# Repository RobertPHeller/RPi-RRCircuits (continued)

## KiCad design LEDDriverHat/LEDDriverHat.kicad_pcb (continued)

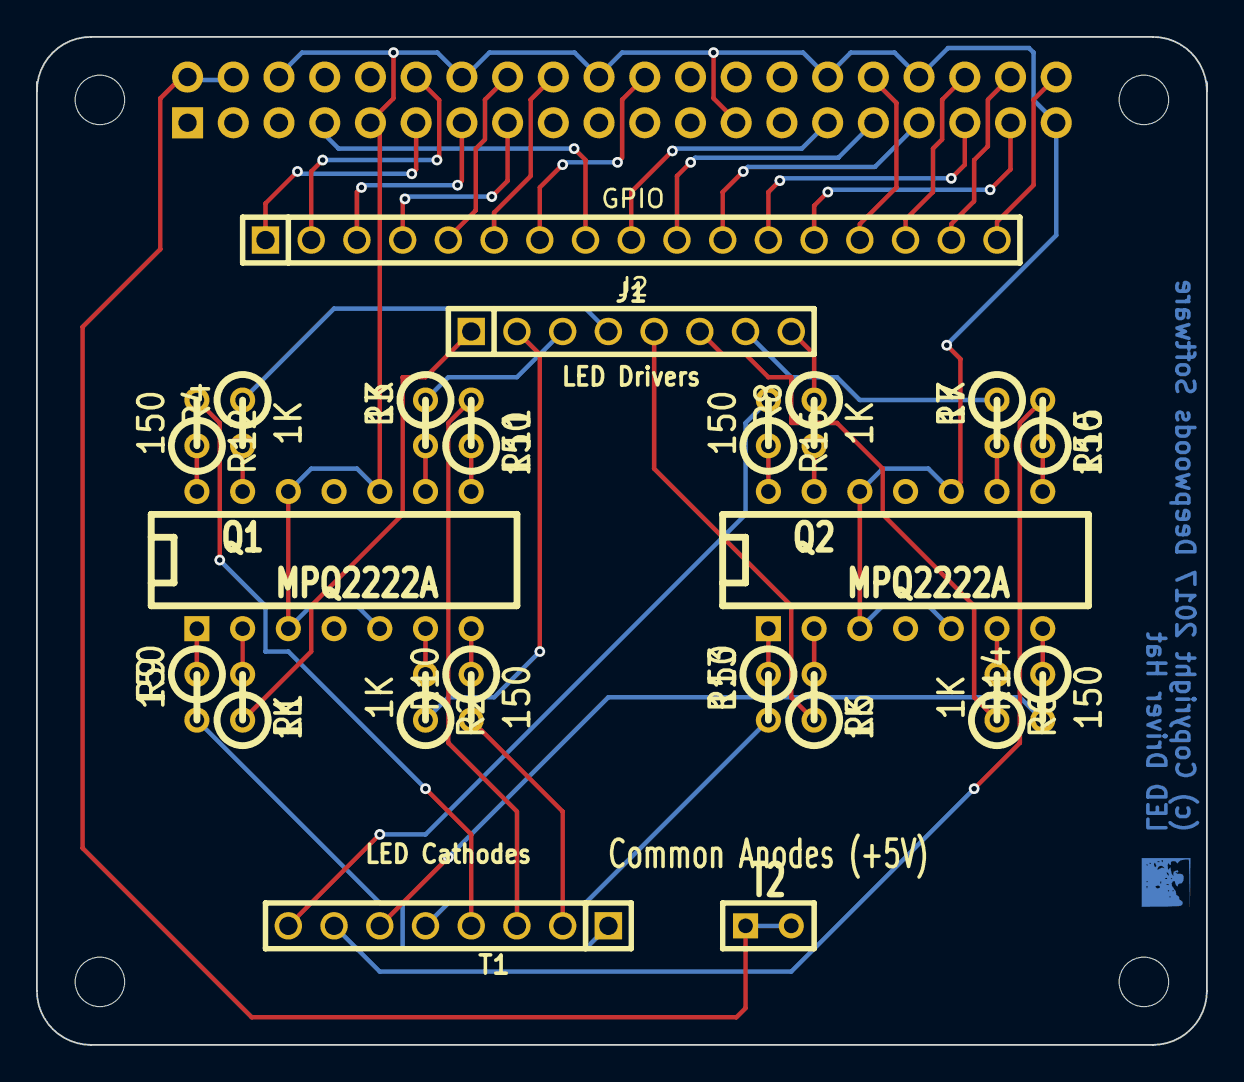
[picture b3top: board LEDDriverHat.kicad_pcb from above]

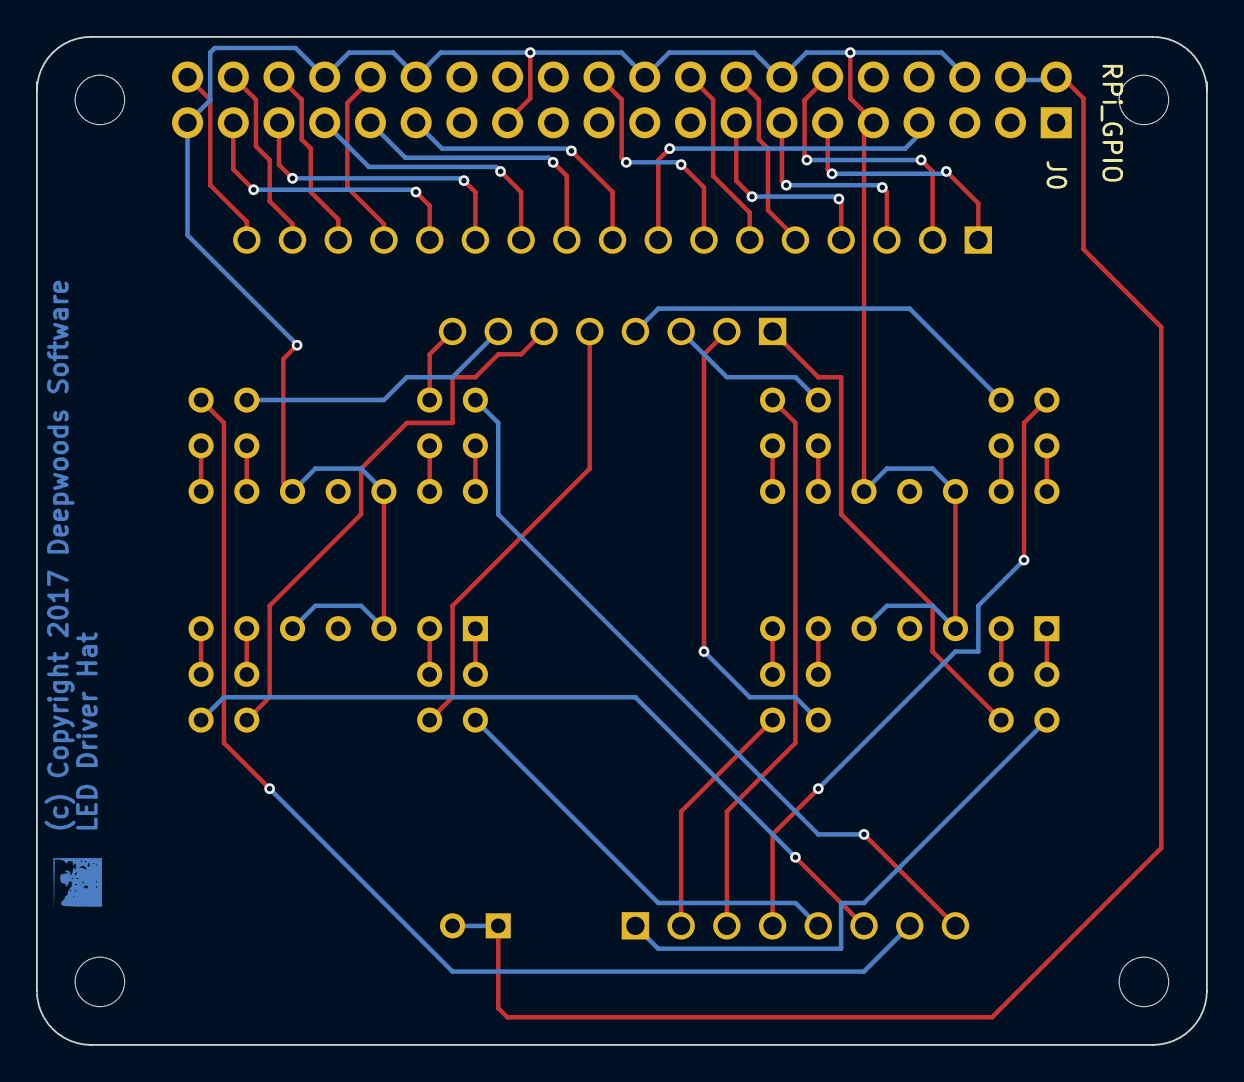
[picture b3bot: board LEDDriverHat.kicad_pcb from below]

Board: 2 copper layers, 65.0 x 56.0 mm, 27 parts (5 on the bottom side), 51 nets.

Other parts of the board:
H1, H2, H3, H4: RPi_Hat_Mounting_Hole

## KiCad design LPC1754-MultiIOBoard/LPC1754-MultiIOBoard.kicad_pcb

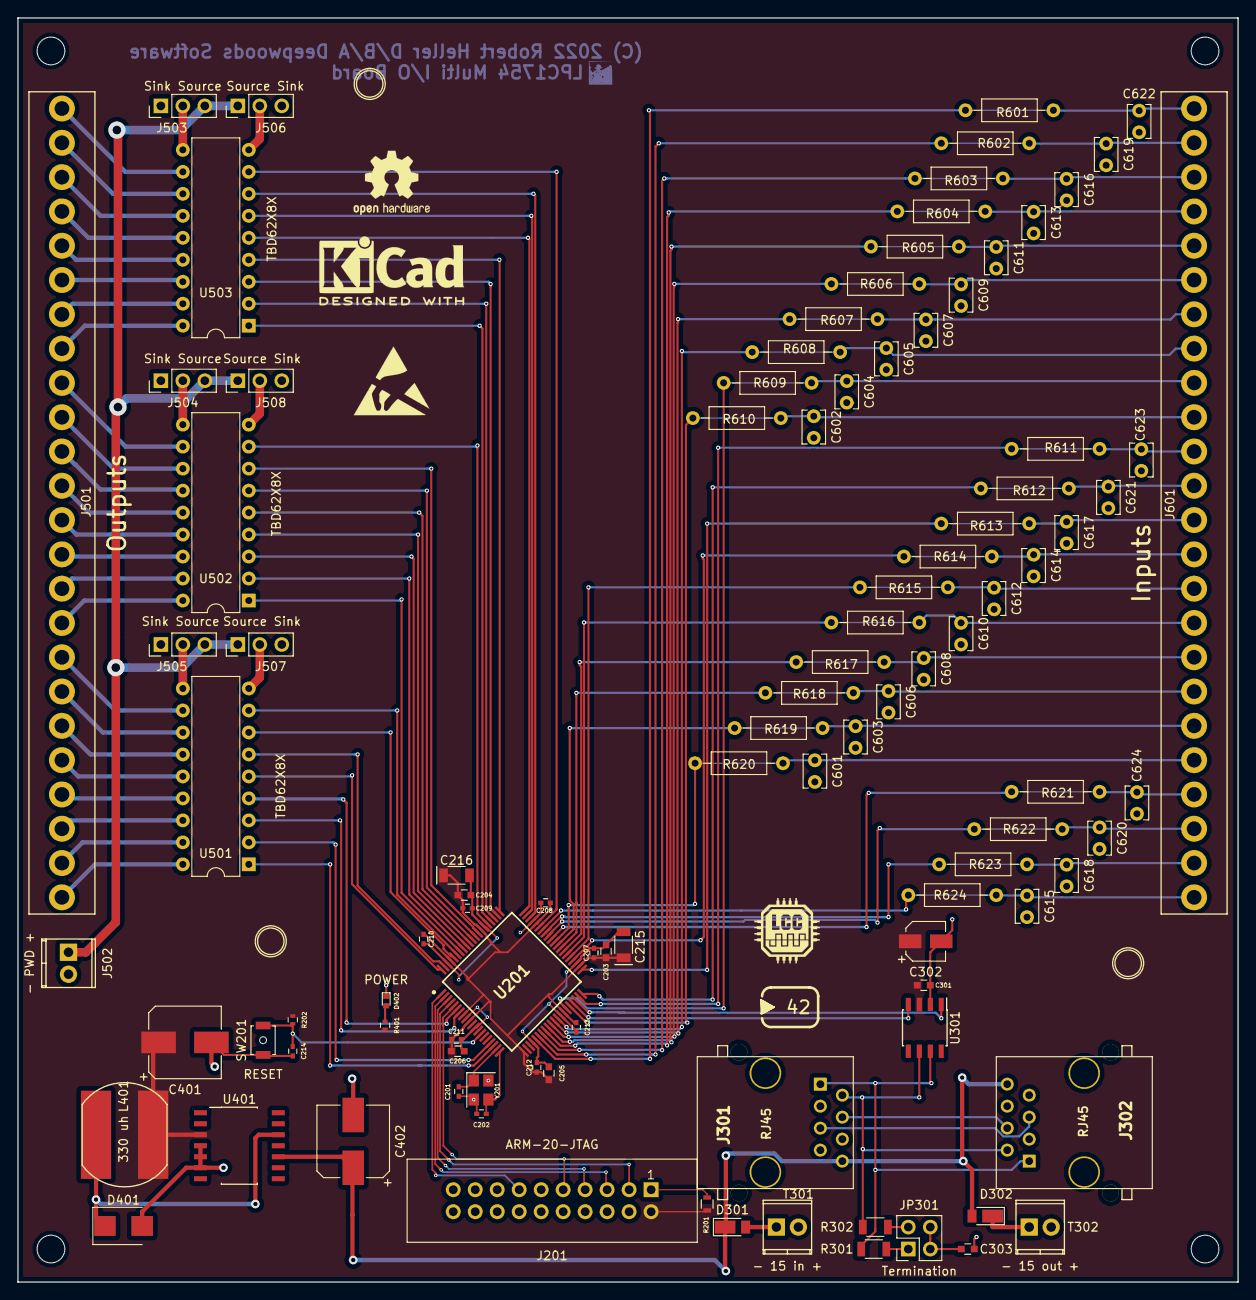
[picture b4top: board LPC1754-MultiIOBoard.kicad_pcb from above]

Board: 2 copper layers, 141.0 x 146.1 mm, 102 parts (0 on the bottom side), 128 nets.

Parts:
C201: 18 pF; C_0402
C202: 18pf; C_0402
C203, C204, C205, C206: 1uf; C_0603
C207, C208, C209, C210, C211, C212, C213: 100nf; C_0402
C214: 1uf; C_0402
C215, C216: 10 uf; C_POL_1206
C301: .1 uf; C_0603
C302: 15 uf 15V; CP_Elec_4x5.7
C303: 47 nf; C_0603
C401: 220 uf 25V; CP_Elec_8x10
C402: 22 uf 100V; CP_Elec_8x10
C601, C602, C603, C604, C605, C606, C607, C608, C609, C610, C611, C612, C613, C614, C615, C616, C617, C618, C619, C620, C621, C622, C623, C624: C; C_Disc_D3.8mm_W2.6mm_P2.50mm
D301, D302: DFLS240-7; D_PowerDI-123
D401: CMSH1-60 TR13; D_SMB
D402: POWER; LED_0402
J201: ARM-20-JTAG; IDC_Header_Straight_20pins
J301, J302: RJ45; RJ45_8N-S
J501: Outputs; Molex_KK_396_01x24_3.96mm_RightAngle
J502: - PWD +; TerminalBlock_Pheonix_MPT-2.54mm_2pol
J503, J504, J505: Sink Source; Pin_Header_Straight_1x03_Pitch2.54mm
J506, J507, J508: Source Sink; Pin_Header_Straight_1x03_Pitch2.54mm
J601: Inputs; Molex_KK_396_01x24_3.96mm_RightAngle
JP301: Termination; Pin_Header_Straight_2x02_Pitch2.54mm
L401: 330 uh; SRN1060
R201: 0; R_0603
R202: 10K; R_0402
R301, R302: 60 Ohms; R_1206
R401: 330; R_0402
R601, R602, R603, R604, R605, R606, R607, R608, R609, R610, R611, R612, R613, R614, R615, R616, R617, R618, R619, R620, R621, R622, R623, R624: 0; R_Axial_DIN0207_L6.3mm_D2.5mm_P10.16mm_Horizontal_WJumper
SW201: RESET; SW_SPST_B3U-1000P-B
T301: - 15 in +; TerminalBlock_Pheonix_MPT-2.54mm_2pol
T302: - 15 out +; TerminalBlock_Pheonix_MPT-2.54mm_2pol
U201: LPC1754FBD80,551; QFP50P1400X1400X160-80N
U301: TCAN332DR; SOIC-8_3.9x4.9mm_Pitch1.27mm
U401: LM2574N-3.3; SOIC-14_7.4x8.7mm_Pitch1.27mm
U501, U502, U503: TBD62X8X; DIP-18_W7.62mm
Y201: 25MHZ; Crystal_SMD_Abracon_ABM8G-4pin_3.2x2.5mm

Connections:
+3V3: C203.1, C204.1, C205.1, C206.1, C207.1, C208.1, C209.1, C210.1, C211.1, C212.1, C213.1, C215.1, C216.1, C301.1, C302.1, C401.1, J201.2, L401.2, R201.2, R202.1, R401.2, U201.8, U201.10, U201.21, U201.34, U201.42, U201.56, U201.67, U201.77, U301.3, U401.3
+VDC: J502.1, J503.3, J504.3, J505.3, J506.1, J507.1, J508.1
/CAN Transceiver/CANH: J301.1, J302.1, R301.1, U301.7
/CAN Transceiver/CANL: J301.2, J302.2, R302.1, U301.6
/CAN Transceiver/CAN_RX: U201.37, U301.4
/CAN Transceiver/CAN_TX: U201.38, U301.1
/Micro Processor Unit/C0P0B0: R601.2, U201.25
/Micro Processor Unit/C0P0B1: R602.2, U201.26
/Micro Processor Unit/C0P0B2: R603.2, U201.27
/Micro Processor Unit/C0P0B3: R604.2, U201.28
/Micro Processor Unit/C0P0B4: R605.2, U201.29
/Micro Processor Unit/C0P0B5: R606.2, U201.30
/Micro Processor Unit/C0P0B6: R607.2, U201.31
/Micro Processor Unit/C0P0B7: R608.2, U201.32
/Micro Processor Unit/C0P1B0: R609.2, U201.35
/Micro Processor Unit/C0P1B1: R610.2, U201.36
/Micro Processor Unit/C0P1B2: R611.2, U201.39
/Micro Processor Unit/C0P1B3: R612.2, U201.40
/Micro Processor Unit/C0P1B4: R613.2, U201.41
/Micro Processor Unit/C0P1B5: R614.2, U201.44
/Micro Processor Unit/C0P1B6: R615.2, U201.45
/Micro Processor Unit/C0P1B7: R616.2, U201.46
/Micro Processor Unit/C0P2B0: R617.2, U201.47
/Micro Processor Unit/C0P2B1: R618.2, U201.48
/Micro Processor Unit/C0P2B2: R619.2, U201.49
/Micro Processor Unit/C0P2B3: R620.2, U201.50
/Micro Processor Unit/C0P2B4: R621.2, U201.51
/Micro Processor Unit/C0P2B5: R622.2, U201.52
/Micro Processor Unit/C0P2B6: R623.2, U201.53
/Micro Processor Unit/C0P2B7: R624.2, U201.54
/Micro Processor Unit/C1P0B0: U201.18, U501.1
/Micro Processor Unit/C1P0B1: U201.17, U501.2
/Micro Processor Unit/C1P0B2: U201.7, U501.3
/Micro Processor Unit/C1P0B3: U201.6, U501.4
/Micro Processor Unit/C1P0B4: U201.80, U501.5
/Micro Processor Unit/C1P0B5: U201.79, U501.6
/Micro Processor Unit/C1P0B6: U201.76, U501.7
/Micro Processor Unit/C1P0B7: U201.75, U501.8
/Micro Processor Unit/C1P1B0: U201.74, U502.1
/Micro Processor Unit/C1P1B1: U201.73, U502.2
/Micro Processor Unit/C1P1B2: U201.72, U502.3
/Micro Processor Unit/C1P1B3: U201.71, U502.4
/Micro Processor Unit/C1P1B4: U201.70, U502.5
/Micro Processor Unit/C1P1B5: U201.69, U502.6
/Micro Processor Unit/C1P1B6: U201.68, U502.7
/Micro Processor Unit/C1P1B7: U201.65, U502.8
/Micro Processor Unit/C1P2B0: U201.64, U503.1
/Micro Processor Unit/C1P2B1: U201.63, U503.2
/Micro Processor Unit/C1P2B2: U201.62, U503.3
/Micro Processor Unit/C1P2B3: U201.61, U503.4
/Micro Processor Unit/C1P2B4: U201.60, U503.5
/Micro Processor Unit/C1P2B5: U201.59, U503.6
/Micro Processor Unit/C1P2B6: U201.58, U503.7
/Micro Processor Unit/C1P2B7: U201.55, U503.8
CAN +12V: C402.1, D301.1, D302.2, J301.8, J302.8, U401.10
GND: C201.2, C202.2, C203.2, C204.2, C205.2, C206.2, C207.2, C208.2, C209.2, C210.2, C211.2, C212.2, C213.2, C214.2, C215.2, C216.2, C301.2, C302.2, C303.2, C401.2, C402.2, C601.2, C602.2, C603.2, C604.2, C605.2, C606.2, C607.2, C608.2, C609.2, C610.2, C611.2, C612.2, C613.2, C614.2, C615.2, C616.2, C617.2, C618.2, C619.2, C620.2, C621.2, C622.2, C623.2, C624.2, D401.2, D402.1, J201.4, J201.6, J201.8, J201.10, J201.12, J201.14, J201.16, J201.18, J201.20, J301.3, J301.6, J301.7, J302.3, J302.6, J302.7, J502.2, J503.1, J504.1, J505.1, J506.3, J507.3, J508.3, SW201.1, T301.2, T302.2, U201.9, U201.12, U201.24, U201.33, U201.43, U201.57, U201.66, U201.78, U301.2, U401.4, U401.5, U401.6, Y201.2, Y201.4
unnamed: C201.1, U201.19, Y201.1
unnamed: C202.1, U201.20, Y201.3
unnamed: C214.1, R202.2, SW201.2, U201.14
unnamed: C303.1, JP301.3, JP301.4
unnamed: C601.1, J601.20, R620.1
unnamed: C602.1, J601.10, R610.1
unnamed: C603.1, J601.19, R619.1
unnamed: C604.1, J601.9, R609.1
unnamed: C605.1, J601.8, R608.1
unnamed: C606.1, J601.18, R618.1
unnamed: C607.1, J601.7, R607.1
unnamed: C608.1, J601.17, R617.1
unnamed: C609.1, J601.6, R606.1
unnamed: C610.1, J601.16, R616.1
unnamed: C611.1, J601.5, R605.1
unnamed: C612.1, J601.15, R615.1
unnamed: C613.1, J601.4, R604.1
unnamed: C614.1, J601.14, R614.1
unnamed: C615.1, J601.24, R624.1
unnamed: C616.1, J601.3, R603.1
unnamed: C617.1, J601.13, R613.1
unnamed: C618.1, J601.23, R623.1
unnamed: C619.1, J601.2, R602.1
unnamed: C620.1, J601.22, R622.1
unnamed: C621.1, J601.12, R612.1
unnamed: C622.1, J601.1, R601.1
unnamed: C623.1, J601.11, R611.1
unnamed: C624.1, J601.21, R621.1
unnamed: D301.2, T301.1
unnamed: D302.1, T302.1
unnamed: D401.1, L401.1, U401.12
unnamed: D402.2, R401.1
unnamed: J201.1, R201.1
unnamed: J201.3, U201.4
unnamed: J201.5, U201.2
unnamed: J201.7, U201.3
unnamed: J201.9, U201.5
unnamed: J201.13, U201.1
unnamed: J301.4, J302.4
unnamed: J301.5, J302.5
unnamed: J501.1, U501.18
unnamed: J501.2, U501.17
unnamed: J501.3, U501.16
unnamed: J501.4, U501.15
unnamed: J501.5, U501.14
unnamed: J501.6, U501.13
unnamed: J501.7, U501.12
unnamed: J501.8, U501.11
unnamed: J501.9, U502.18
unnamed: J501.10, U502.17
unnamed: J501.11, U502.16
unnamed: J501.12, U502.15
unnamed: J501.13, U502.14
unnamed: J501.14, U502.13
unnamed: J501.15, U502.12
unnamed: J501.16, U502.11
unnamed: J501.17, U503.18
unnamed: J501.18, U503.17
unnamed: J501.19, U503.16
unnamed: J501.20, U503.15
unnamed: J501.21, U503.14
unnamed: J501.22, U503.13
unnamed: J501.23, U503.12
unnamed: J501.24, U503.11
unnamed: J503.2, U503.10
unnamed: J504.2, U502.10
unnamed: J505.2, U501.10
unnamed: J506.2, U503.9
unnamed: J507.2, U501.9
unnamed: J508.2, U502.9
unnamed: JP301.1, R301.2
unnamed: JP301.2, R302.2

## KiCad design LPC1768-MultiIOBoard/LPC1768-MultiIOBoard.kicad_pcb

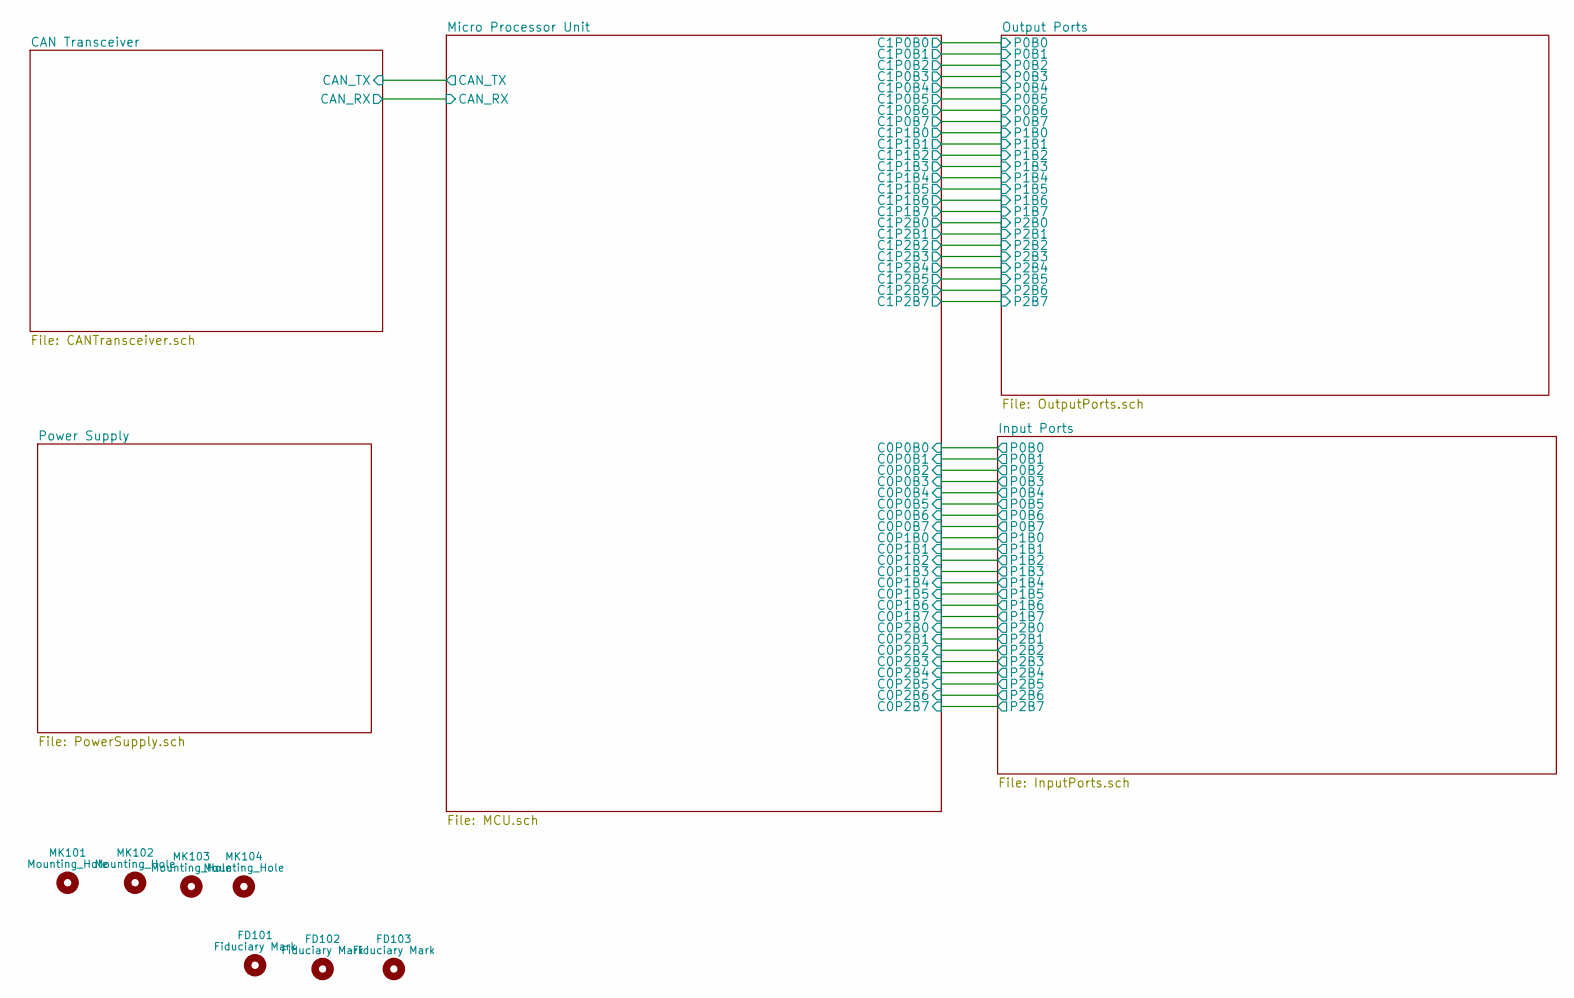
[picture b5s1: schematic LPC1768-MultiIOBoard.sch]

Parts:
FD101, FD102, FD103: Fiduciary Mark; Fiducial_classic_Small_SilkscreenTop_Type1
MK101, MK102, MK103, MK104: Mounting_Hole; MountingHole_3.2mm_M3

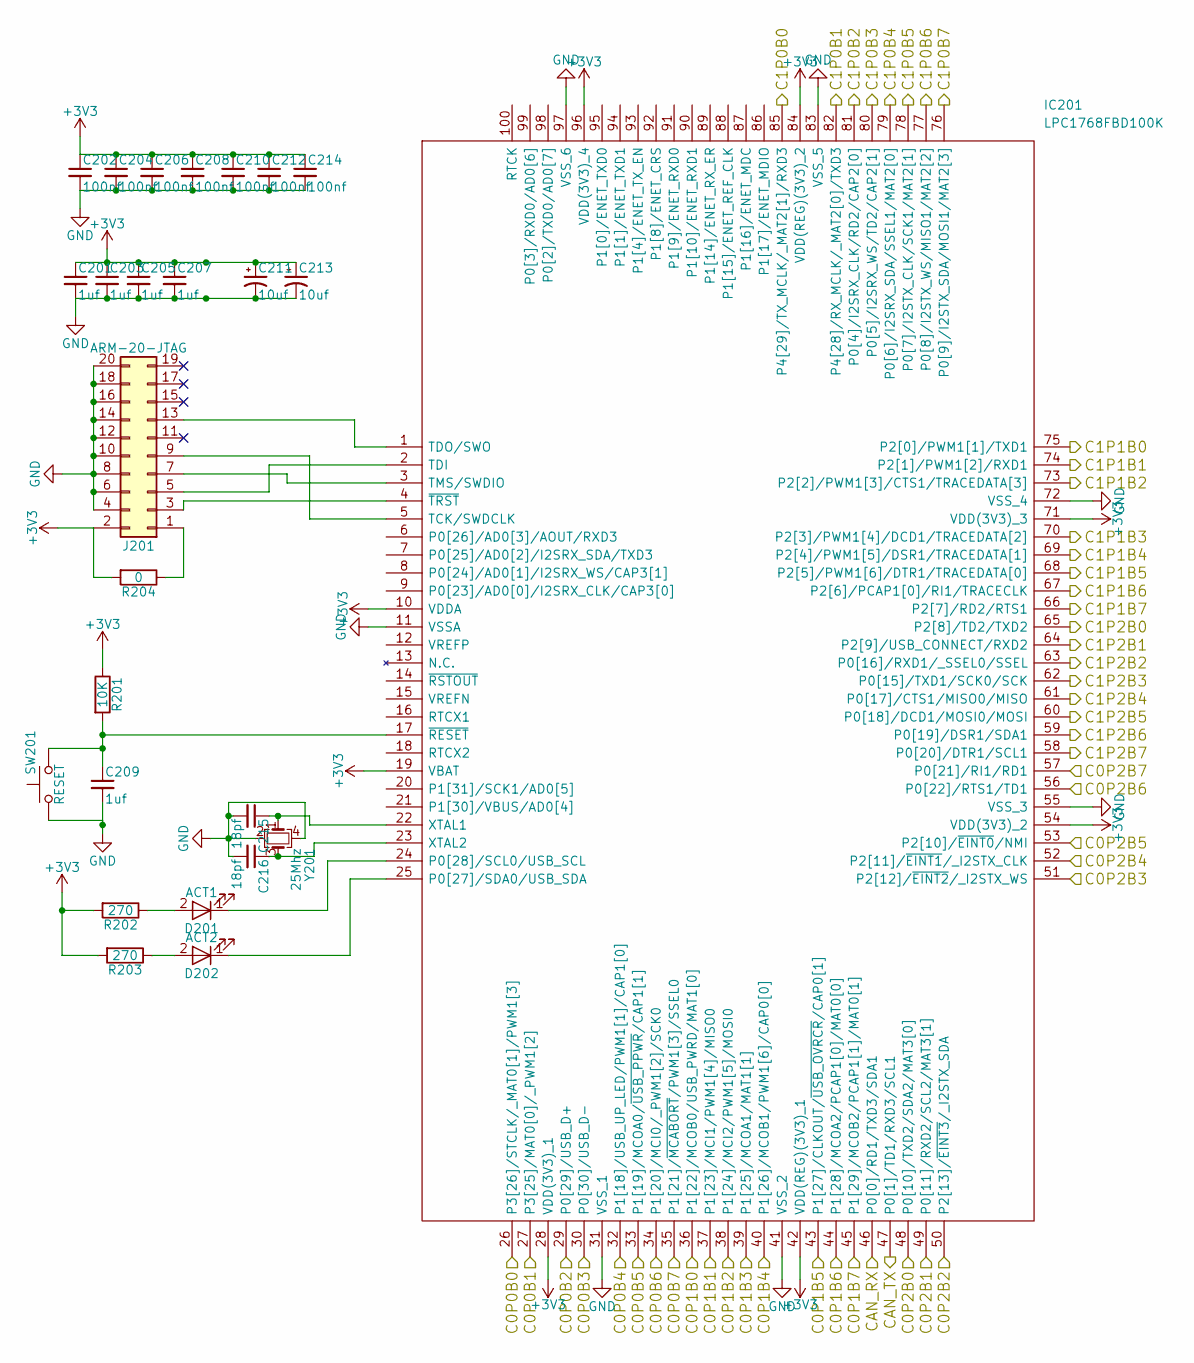
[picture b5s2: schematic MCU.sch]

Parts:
C201, C203, C205, C207, C209: 1uf; C_0603
C202, C204, C206, C208, C210, C212, C214: 100nf; C_0402
C211, C213: 10uf; C_POL_1206
C215, C216: 18pf; C_0402; Mouser Part Number 81-GCM1555C1H180JA6J
D201: ACT1; LED_0402
D202: ACT2; LED_0402
IC201: LPC1768FBD100K; QFP50P1600X1600X160-100N; Manufacturer_Part_Number LPC1768FBD100K
J201: ARM-20-JTAG; IDC_Header_Straight_20pins
R201: 10K; R_0402
R202, R203: 270; R_0402
R204: 0; R_0402
SW201: RESET; SW_SPST_B3U-1000P-B; Mouser Part Number 653-B3U-1000P-B
Y201: 25Mhz; Crystal_SMD_Abracon_ABM8G-4pin_3.2x2.5mm; Mouser Part Number 815-ABM8G-25-4YT3

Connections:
/CAN Transceiver/CAN_RX: IC201.46 (P0[0]/RD1/TXD3/SDA1); also elsewhere on the board
/CAN Transceiver/CAN_TX: IC201.47 (P0[1]/TD1/RXD3/SCL1); also elsewhere on the board
/Micro Processor Unit/C0P0B0: IC201.26 (P3[26]/STCLK/_MAT0[1]/PWM1[3]); also elsewhere on the board
/Micro Processor Unit/C0P0B1: IC201.27 (P3[25]/MAT0[0]/_PWM1[2]); also elsewhere on the board
/Micro Processor Unit/C0P0B2: IC201.29 (P0[29]/USB_D+); also elsewhere on the board
/Micro Processor Unit/C0P0B3: IC201.30 (P0[30]/USB_D-); also elsewhere on the board
/Micro Processor Unit/C0P0B4: IC201.32 (P1[18]/USB_UP_LED/PWM1[1]/CAP1[0]); also elsewhere on the board
/Micro Processor Unit/C0P0B5: IC201.33 (P1[19]/MCOA0/~USB_PPWR~/CAP1[1]); also elsewhere on the board
/Micro Processor Unit/C0P0B6: IC201.34 (P1[20]/MCI0/_PWM1[2]/SCK0); also elsewhere on the board
/Micro Processor Unit/C0P0B7: IC201.35 (P1[21]/~MCABORT~/PWM1[3]/SSEL0); also elsewhere on the board
/Micro Processor Unit/C0P1B0: IC201.36 (P1[22]/MCOB0/USB_PWRD/MAT1[0]); also elsewhere on the board
/Micro Processor Unit/C0P1B1: IC201.37 (P1[23]/MCI1/PWM1[4]/MISO0); also elsewhere on the board
/Micro Processor Unit/C0P1B2: IC201.38 (P1[24]/MCI2/PWM1[5]/MOSI0); also elsewhere on the board
/Micro Processor Unit/C0P1B3: IC201.39 (P1[25]/MCOA1/MAT1[1]); also elsewhere on the board
/Micro Processor Unit/C0P1B4: IC201.40 (P1[26]/MCOB1/PWM1[6]/CAP0[0]); also elsewhere on the board
/Micro Processor Unit/C0P1B5: IC201.43 (P1[27]/CLKOUT/~USB_OVRCR~/CAP0[1]); also elsewhere on the board
/Micro Processor Unit/C0P1B6: IC201.44 (P1[28]/MCOA2/PCAP1[0]/MAT0[0]); also elsewhere on the board
/Micro Processor Unit/C0P1B7: IC201.45 (P1[29]/MCOB2/PCAP1[1]/MAT0[1]); also elsewhere on the board
/Micro Processor Unit/C0P2B0: IC201.48 (P0[10]/TXD2/SDA2/MAT3[0]); also elsewhere on the board
/Micro Processor Unit/C0P2B1: IC201.49 (P0[11]/RXD2/SCL2/MAT3[1]); also elsewhere on the board
/Micro Processor Unit/C0P2B2: IC201.50 (P2[13]/~EINT3~/_I2STX_SDA); also elsewhere on the board
/Micro Processor Unit/C0P2B3: IC201.51 (P2[12]/~EINT2~/_I2STX_WS); also elsewhere on the board
/Micro Processor Unit/C0P2B4: IC201.52 (P2[11]/~EINT1~/_I2STX_CLK); also elsewhere on the board
/Micro Processor Unit/C0P2B5: IC201.53 (P2[10]/~EINT0~/NMI); also elsewhere on the board
/Micro Processor Unit/C0P2B6: IC201.56 (P0[22]/RTS1/TD1); also elsewhere on the board
/Micro Processor Unit/C0P2B7: IC201.57 (P0[21]/RI1/RD1); also elsewhere on the board
/Micro Processor Unit/C1P0B0: IC201.85 (P4[29]/TX_MCLK/_MAT2[1]/RXD3); also elsewhere on the board
/Micro Processor Unit/C1P0B1: IC201.82 (P4[28]/RX_MCLK/_MAT2[0]/TXD3); also elsewhere on the board
/Micro Processor Unit/C1P0B2: IC201.81 (P0[4]/I2SRX_CLK/RD2/CAP2[0]); also elsewhere on the board
/Micro Processor Unit/C1P0B3: IC201.80 (P0[5]/I2SRX_WS/TD2/CAP2[1]); also elsewhere on the board
/Micro Processor Unit/C1P0B4: IC201.79 (P0[6]/I2SRX_SDA/SSEL1/MAT2[0]); also elsewhere on the board
/Micro Processor Unit/C1P0B5: IC201.78 (P0[7]/I2STX_CLK/SCK1/MAT2[1]); also elsewhere on the board
/Micro Processor Unit/C1P0B6: IC201.77 (P0[8]/I2STX_WS/MISO1/MAT2[2]); also elsewhere on the board
/Micro Processor Unit/C1P0B7: IC201.76 (P0[9]/I2STX_SDA/MOSI1/MAT2[3]); also elsewhere on the board
/Micro Processor Unit/C1P1B0: IC201.75 (P2[0]/PWM1[1]/TXD1); also elsewhere on the board
/Micro Processor Unit/C1P1B1: IC201.74 (P2[1]/PWM1[2]/RXD1); also elsewhere on the board
/Micro Processor Unit/C1P1B2: IC201.73 (P2[2]/PWM1[3]/CTS1/TRACEDATA[3]); also elsewhere on the board
/Micro Processor Unit/C1P1B3: IC201.70 (P2[3]/PWM1[4]/DCD1/TRACEDATA[2]); also elsewhere on the board
/Micro Processor Unit/C1P1B4: IC201.69 (P2[4]/PWM1[5]/DSR1/TRACEDATA[1]); also elsewhere on the board
/Micro Processor Unit/C1P1B5: IC201.68 (P2[5]/PWM1[6]/DTR1/TRACEDATA[0]); also elsewhere on the board
/Micro Processor Unit/C1P1B6: IC201.67 (P2[6]/PCAP1[0]/RI1/TRACECLK); also elsewhere on the board
/Micro Processor Unit/C1P1B7: IC201.66 (P2[7]/RD2/RTS1); also elsewhere on the board
/Micro Processor Unit/C1P2B0: IC201.65 (P2[8]/TD2/TXD2); also elsewhere on the board
/Micro Processor Unit/C1P2B1: IC201.64 (P2[9]/USB_CONNECT/RXD2); also elsewhere on the board
/Micro Processor Unit/C1P2B2: IC201.63 (P0[16]/RXD1/_SSEL0/SSEL); also elsewhere on the board
/Micro Processor Unit/C1P2B3: IC201.62 (P0[15]/TXD1/SCK0/SCK); also elsewhere on the board
/Micro Processor Unit/C1P2B4: IC201.61 (P0[17]/CTS1/MISO0/MISO); also elsewhere on the board
/Micro Processor Unit/C1P2B5: IC201.60 (P0[18]/DCD1/MOSI0/MOSI); also elsewhere on the board
/Micro Processor Unit/C1P2B6: IC201.59 (P0[19]/DSR1/SDA1); also elsewhere on the board
/Micro Processor Unit/C1P2B7: IC201.58 (P0[20]/DTR1/SCL1); also elsewhere on the board
GND: C201.2, C202.2, C203.2, C204.2, C205.2, C206.2, C207.2, C208.2, C209.2, C210.2, C211.2, C212.2, C213.2, C214.2, C215.2, C216.2, IC201.11 (VSSA), IC201.31 (VSS_1), IC201.41 (VSS_2), IC201.55 (VSS_3), IC201.72 (VSS_4), IC201.83 (VSS_5), IC201.97 (VSS_6), J201.4, J201.6, J201.8, J201.10, J201.12, J201.14, J201.16, J201.18, J201.20, SW201.1, Y201.2, Y201.4; also elsewhere on the board
unnamed: C209.1, IC201.17 (~RESET), R201.2, SW201.2
unnamed: C215.1, IC201.22 (XTAL1), Y201.1
unnamed: C216.1, IC201.23 (XTAL2), Y201.3
unnamed: D201.1 (K), IC201.24 (P0[28]/SCL0/USB_SCL)
unnamed: D201.2 (A), R202.1
unnamed: D202.1 (K), IC201.25 (P0[27]/SDA0/USB_SDA)
unnamed: D202.2 (A), R203.1
unnamed: IC201.1 (TDO/SWO), J201.13
unnamed: IC201.2 (TDI), J201.5
unnamed: IC201.3 (TMS/SWDIO), J201.7
unnamed: IC201.4 (~TRST), J201.3
unnamed: IC201.5 (TCK/SWDCLK), J201.9
unnamed: J201.1, R204.1

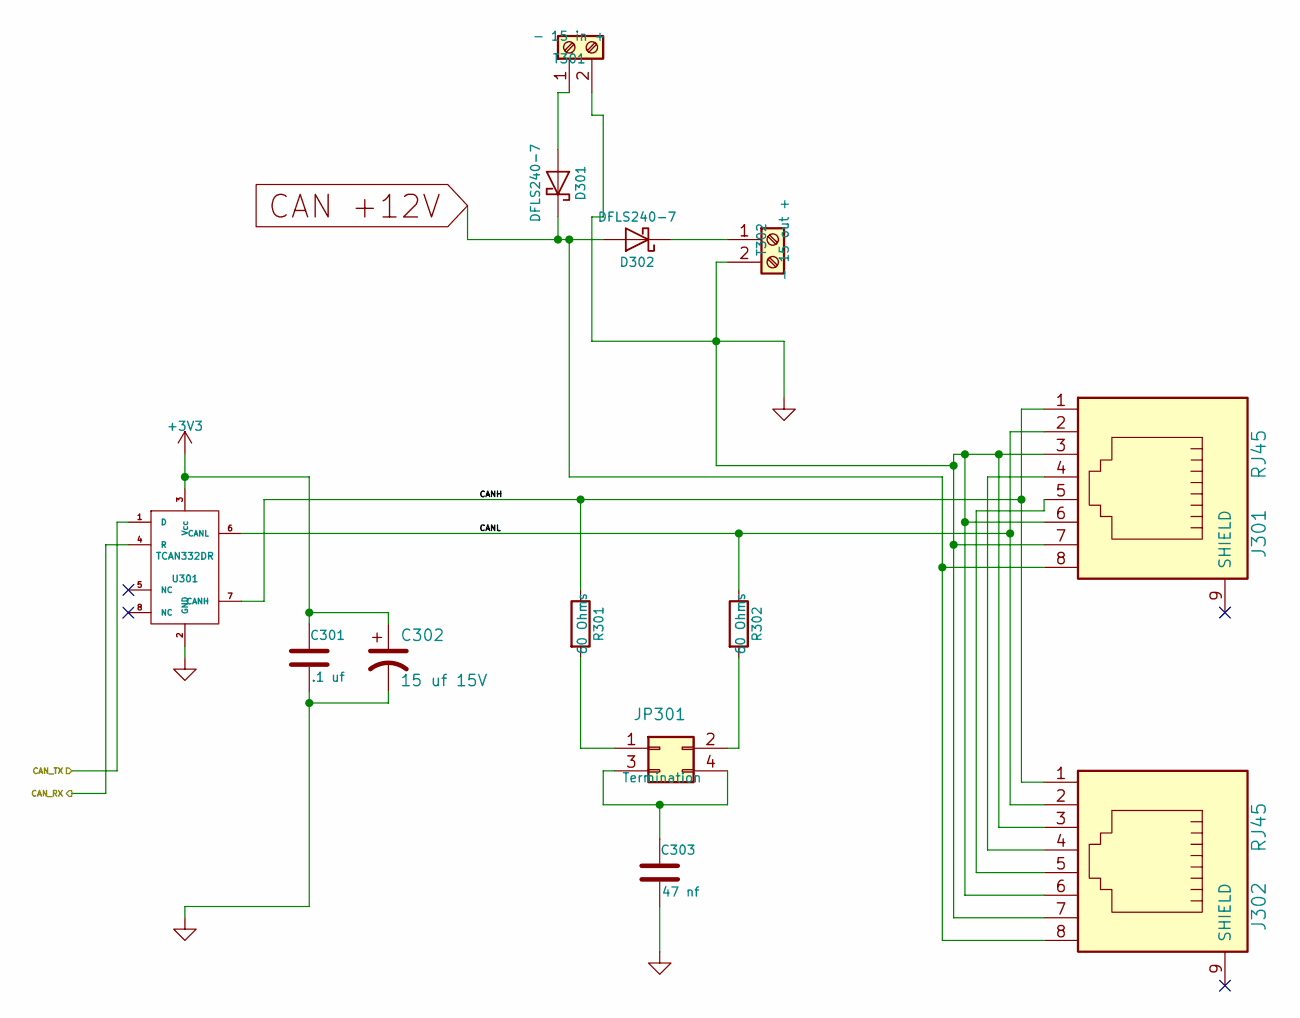
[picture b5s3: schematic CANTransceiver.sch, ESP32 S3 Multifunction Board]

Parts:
C301: .1 uf; C_0603; Mouser Part Number 710-885012206095
C302: 15 uf 15V; CP_Elec_4x5.7; Mouser Part Number 647-UUD1C150MCL
C303: 47 nf; C_0603; Mouser Part Number 710-885012206093
D301, D302: DFLS240-7; D_PowerDI-123; Mouser Part Number 621-DFLS240-7
J301, J302: RJ45; RJ45_8N-S; Mouser Part Number 710-615008144221
JP301: Termination; Pin_Header_Straight_2x02_Pitch2.54mm; Mouser Part Number 649-67997-404HLF
R301, R302: 60 Ohms; R_1206; Mouser Part Number 71-CRCW120660R0KNAIF
T301: - 15 in +; TerminalBlock_Pheonix_MPT-2.54mm_2pol; Mouser Part Number 651-1725656
T302: - 15 out +; TerminalBlock_Pheonix_MPT-2.54mm_2pol; Mouser Part Number 651-1725656
U301: TCAN332DR; SOIC-8_3.9x4.9mm_Pitch1.27mm; Mouser Part Number 595-TCAN332DR

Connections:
/CAN Transceiver/CANH: J301.1, J302.1, R301.1, U301.7 (CANH)
/CAN Transceiver/CANL: J301.2, J302.2, R302.1, U301.6 (CANL)
/CAN Transceiver/CAN_RX: U301.4 (R); also elsewhere on the board
/CAN Transceiver/CAN_TX: U301.1 (D); also elsewhere on the board
CAN +12V: D301.1 (K), D302.2 (A), J301.8, J302.8; also elsewhere on the board
GND: C301.2, C302.2, C303.2, J301.3, J301.6, J301.7, J302.3, J302.6, J302.7, T301.2, T302.2, U301.2 (GND); also elsewhere on the board
unnamed: C303.1, JP301.3, JP301.4
unnamed: D301.2 (A), T301.1
unnamed: D302.1 (K), T302.1
unnamed: J301.4, J302.4
unnamed: J301.5, J302.5
unnamed: JP301.1, R301.2
unnamed: JP301.2, R302.2

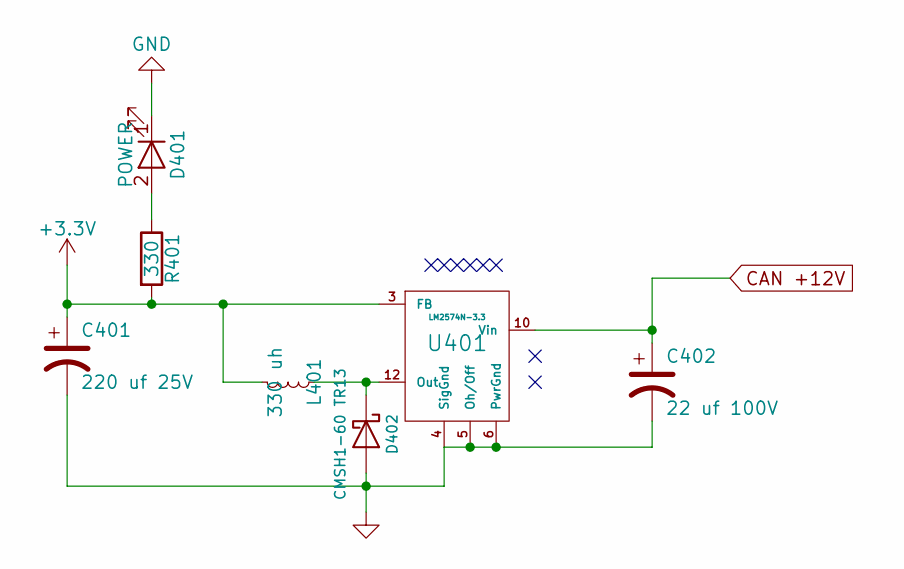
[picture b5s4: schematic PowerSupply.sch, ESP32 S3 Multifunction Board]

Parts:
C401: 220 uf 25V; CP_Elec_8x10; Mouser Part Number 647-UWT1E221MNL1GS
C402: 22 uf 100V; CP_Elec_8x10; Mouser Part Number 647-UUX2A220MNL6GS
D401: POWER; LED_0402
D402: CMSH1-60 TR13; D_SMB; Mouser Part Number 610-CMSH1-60TR13
L401: 330 uh; SRN1060; Mouser Part Number 652-SRN1060-331M
R401: 330; R_0402
U401: LM2574N-3.3; SOIC-14_7.4x8.7mm_Pitch1.27mm; Mouser Part Number 926-LM2574MX33NOPB

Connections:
CAN +12V: C402.1, U401.10 (Vin); also elsewhere on the board
GND: C401.2, C402.2, D401.1 (K), D402.2 (A), U401.4 (SigGnd), U401.5 (Oh/Off), U401.6 (PwrGnd); also elsewhere on the board
unnamed: D401.2 (A), R401.1
unnamed: D402.1 (K), L401.1, U401.12 (Out)
